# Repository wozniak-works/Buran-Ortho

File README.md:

# Buran-Ortho
A 39-key orthogonal keyboard with support for two knobs.
Forked version with hotswap sockets.

Used License :: [Cern Open hardware](/LICENSE)

---

## Status :: 
- Rev 3 released
- Case options were updated accordingly 
- untested LED-Pinout 

---

## Features :: 
- PCB supports MX, Alps and Choc v1 switches  
- QMK and Vial Support
- built with rp2040 and additional flash storage allowing for plenty of combos, layers, led matrices etc.
- easy to order with jlcpcb --> check release for files 
- support up to two encoders 
- additional pinouts for further modifications 
- - technically could fit an OLED or some other additional parts
- gasket mounted case
- case designed for 3d printing 
- several layout-options for middle part.

## Layout :: 
Below all possible layouts can be observed. All the observed layouts can be choosen and used with Vial or Qmk 

## Case :: 
All files for the case are to be found [here](/case/). 

For the top-part of the case there are several options available, where each of them was designed for a specific layout. 

Another **beautiful** case is to be found [here](https://github.com/subottimale/Buran-Bofa-case). Maybe consider it, seems to be constructed better overall.

## Firmware :: 

the pre-compiled file for Vial and the whole Qmk-userspace for this keyboard can be found [here](/firmware/)

To enter the bootloader - which is necessary in order to flash a new firmware - press the button next to the encoder on the back of the pcb and plug-it into your keyboard while keeping the button pressed. It should show up as a regular usb-stick in your file explorer now and you can drag the .utf onto this usb-stick. Once done it will restart and use your newly flashed firmware!

--- 

## Building your own :: 

On the verge to build this keyboard your own?
Below you can find a little guideline on what is required and how to obtain everything: 

### Getting PCBs ::
in the directory **production** you can find both the gerber and POS-Files required for assembly. 
I usually use JLCPCB for my prototypes, the procedure should be fairly similiar for other manufacturers however, and they require the gerber_buran_pcb.zip and for assembly of all SMD-components also their positions (buran-pos-bottom.csv) and the BOM (buran-BOM.csv) all of which can be found in the **production/assembly** directory. 

### Building Case :: 
The case consists of three parts: the bottom-part, top-part (various layouts available) and the plate. 
Print all of them yourself or have someone print them for your (JLCPCB also offers MFJ printing which could be used (**althought untested!**)).
Now to assemble the case you further need:
| Part | Quantity |
|------|----------|
|2mm thick foam to use as gasket| 14x cut pieces | 
| 20mm M3 | 8x | 

> The length for the Gasket can be taken from the existing cutouts in the case 

As alternative one could also replace the screws with small 3mm diameter magnets. 

### Building the board ::
1. Prepare your pcb accordingly. 
2. Further add the plate and position your switches with them, later solder them to the pcb. 
3. add any feature, like LEDS or knobs. 
4. add **the cut foam** to each lip of the plate. It ought to be positioned both at the top and bottom of the plate --> to isolate properly from the rest of the case!
5. Position everything and screw the case together. 
6. Run Vial on your system and configure the keyboard accordingly 

## Images of Case :: 

Case-option for additional acrylic : 

Case-option without additoinal buttons in the middle : 

Image by Isp 

Case-option with an alternative bottom design :

Design and Image by DeadCatAlive

## Images of PCB ::

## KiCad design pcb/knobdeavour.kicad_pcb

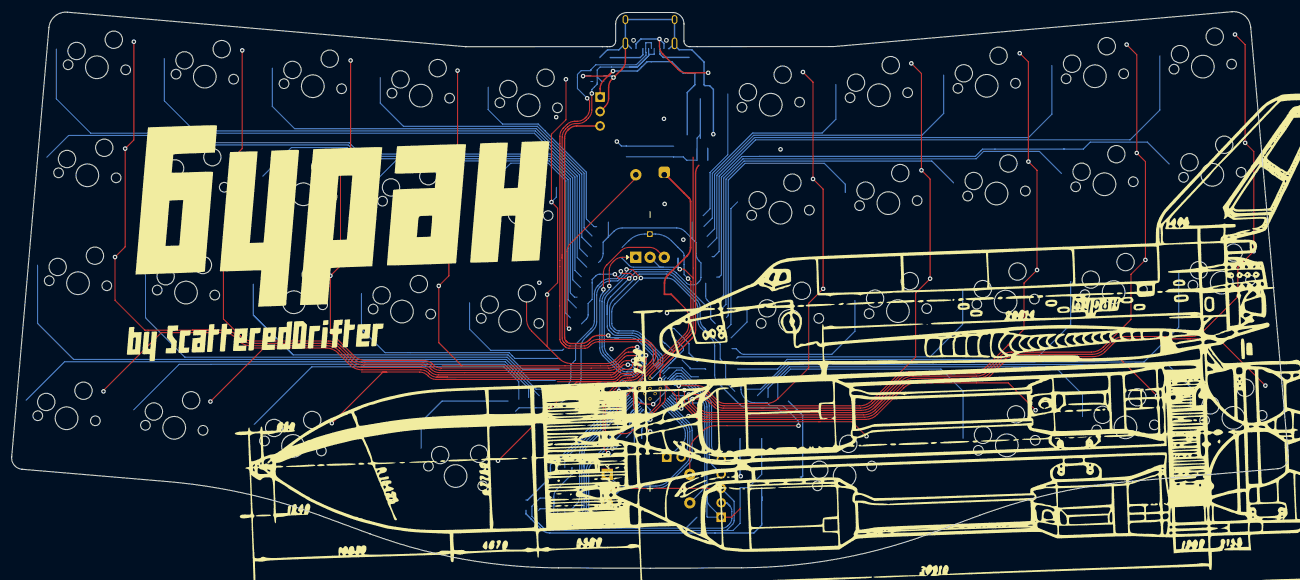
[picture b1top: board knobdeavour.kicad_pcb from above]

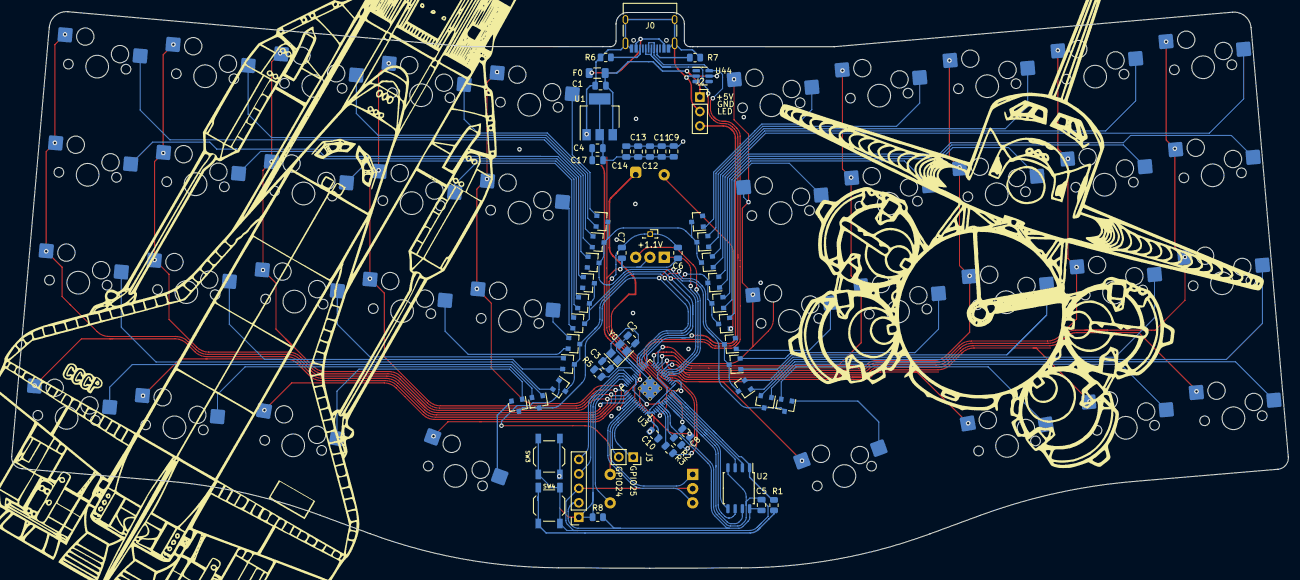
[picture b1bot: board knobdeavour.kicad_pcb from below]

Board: 2 copper layers, 224.4 x 97.8 mm, 97 parts (57 on the bottom side), 87 nets.

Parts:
C1, C4, C17: 10u; C_0805_2012Metric
C2, C3: 22pf; C_0805_2012Metric
C5, C6, C7, C9, C11, C12, C13, C14: 100n; C_0805_2012Metric
C8, C10: 1u; C_0805_2012Metric
D1, D2, D3, D4, D5, D6, D7, D8, D9, D10, D11, D12, D13, D14, D15, D16, D17, D18, D19, D20, D21, D22: BAV70; SOT-23
F0: polyfuse; Fuse_1206_3216Metric
J0: USB_C_Receptacle_USB2.0; USB_C_Receptacle_HRO_TYPE-C-31-M-12
J1: BREAKOUT; PinSocket_1x05_P2.54mm_Vertical
J2: Conn_01x03_Male; PinSocket_1x03_P2.54mm_Vertical
J3: Conn_01x02_Female; PinSocket_1x02_P2.54mm_Vertical
J4: Conn_01x01_Male; PinSocket_1x01_P1.27mm_Vertical
K1, K2, K3, K4, K5, K6, K7, K8, K9, K10, K11, K12, K13, K14, K15, K16, K17, K18, K19, K20, K24, K25, K26, K27, K28, K29, K30, K31, K32, K33, K34, K35, K36, K37, K38, K39, K40, K41: KEYSW; MX100H_modified
R1, R5: 1k; R_0805_2012Metric
R2, R3: 27; R_0805_2012Metric
R6, R7: 5.1k; R_0805_2012Metric
R8: 10K; R_0805_2012Metric
SW1, SW2: RotaryEncoder_Switch; RotaryEncoder_EC11
SW3: SW_PUSH; SW_SPST_TL3342
SW4: RESET; SW_SPST_TL3342
U1: NCP1117-3.3_SOT223; SOT-223-3_TabPin2
U2: W25Q128JVS; SOIC-8_5.23x5.23mm_P1.27mm
U3: RP2040; RP2040-QFN-56
U44: SRV05-4; SOT-23-6
Y0: 12MHZ Crystal; Crystal_SMD_3225-4Pin_3.2x2.5mm

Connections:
+1V1: C6.1, C7.1, C8.1, J4.1, U3.23 (DVDD), U3.45 (VREG_VOUT), U3.50 (DVDD)
+3V3: C4.1, C5.1, C9.1, C10.1, C11.1, C12.1, C13.1, C14.1, C17.1, J1.2, R8.2, U1.2 (VO), U2.8 (VCC), U3.1 (IOVDD), U3.10 (IOVDD), U3.22 (IOVDD), U3.33 (IOVDD), U3.42 (IOVDD), U3.43 (ADC_AVDD), U3.44 (VREG_IN), U3.48 (USB_VDD), U3.49 (IOVDD)
+5V: C1.1, F0.2, J2.1, U1.3 (VI), U44.5 (VP)
/QSPI_SCLK: U2.6 (CLK), U3.52 (QSPI_SCLK)
/QSPI_SD0: U2.5 (DI(IO0)), U3.53 (QSPI_SD0)
/QSPI_SD1: U2.2 (DO(IO1)), U3.55 (QSPI_SD1)
/QSPI_SD2: U2.3 (IO2), U3.54 (QSPI_SD2)
/QSPI_SD3: U2.7 (IO3), U3.51 (QSPI_SD3)
/QSPI_SS: R1.1, U2.1 (~CS), U3.56 (QSPI_SS)
/RUN: J1.1, R8.1, SW3.2, U3.26 (RUN)
/SWCLK: J1.5, U3.24 (SWCLK)
/SWD: J1.4, U3.25 (SWD)
/USB_D+: J0.A6 (D+), J0.B6 (D+), R2.1, U44.3 (IO2)
/USB_D-: J0.A7 (D-), J0.B7 (D-), R3.1, U44.6 (IO4)
/XIN: C2.1, U3.20 (XIN), Y0.3
/XOUT: R5.1, U3.21 (XOUT)
/~USB_BOOT: R1.2, SW4.2
COL0: K1.1, K2.1, K3.1, K4.1, U3.9 (GPIO7)
COL1: K5.1, K6.1, K7.1, K8.1, U3.11 (GPIO8)
COL2: K9.1, K10.1, K11.1, K12.1, U3.12 (GPIO9)
COL3: K13.1, K14.1, K15.1, K16.1, U3.14 (GPIO11)
COL4: K17.1, K18.1, K19.1, U3.13 (GPIO10)
COL5: SW2.S1, U3.2 (GPIO0)
COL6: K25.1, K26.1, K27.1, K28.1, U3.28 (GPIO17)
COL7: K29.1, K30.1, K31.1, K32.1, U3.29 (GPIO18)
COL8: K33.1, K34.1, K35.1, K36.1, U3.30 (GPIO19)
COL9: K37.1, K38.1, K39.1, K40.1, U3.31 (GPIO20)
COL10: K20.1, K24.1, K41.1, U3.32 (GPIO21)
GND: C1.2, C2.2, C3.2, C4.2, C5.2, C6.2, C7.2, C8.2, C9.2, C10.2, C11.2, C12.2, C13.2, C14.2, C17.2, J0.A1 (GND), J0.A12 (GND), J0.B1 (GND), J0.B12 (GND), J0.S1 (SHIELD), J1.3, J2.2, R6.2, R7.2, SW1.C, SW2.C, SW3.1, SW4.1, U1.1 (GND), U2.4 (GND), U3.19 (TESTEN), U3.57 (GND), U44.2 (VN), Y0.2, Y0.4
KNOB2_L: SW2.A, U3.7 (GPIO5)
KNOB2_R: SW2.B, U3.6 (GPIO4)
KNOB2_ROW: D10.1 (A), SW2.S2
KNOB_COL: SW1.S1, U3.27 (GPIO16)
KNOB_DIODE: D22.1 (A), SW1.S2
KNOB_L: SW1.A, U3.35 (GPIO23)
KNOB_R: SW1.B, U3.34 (GPIO22)
LED_GLOW: J2.3, U3.15 (GPIO12)
unnamed: C3.1, R5.2, Y0.1
unnamed: D1.1 (A), K1.2
unnamed: D1.2 (A), K5.2
unnamed: D2.1 (A), K6.2
unnamed: D2.2 (A), K2.2
unnamed: D3.1 (A), K3.2
unnamed: D3.2 (A), K7.2
unnamed: D4.1 (A), K8.2
unnamed: D4.2 (A), K4.2
unnamed: D5.1 (A), K9.2
unnamed: D5.2 (A), K13.2
unnamed: D6.1 (A), K14.2
unnamed: D6.2 (A), K10.2
unnamed: D7.1 (A), K11.2
unnamed: D7.2 (A), K15.2
unnamed: D8.1 (A), K16.2
unnamed: D8.2 (A), K12.2
unnamed: D9.1 (A), K17.2
unnamed: D10.2 (A), K18.2
unnamed: D11.1 (A), K19.2
unnamed: D12.1 (A), K20.2
unnamed: D13.1 (A), K25.2
unnamed: D13.2 (A), K29.2
unnamed: D14.1 (A), K30.2
unnamed: D14.2 (A), K26.2
unnamed: D15.1 (A), K27.2
unnamed: D15.2 (A), K31.2
unnamed: D16.1 (A), K32.2
unnamed: D16.2 (A), K28.2
unnamed: D17.1 (A), K33.2
unnamed: D17.2 (A), K37.2
unnamed: D18.1 (A), K38.2
unnamed: D18.2 (A), K34.2
unnamed: D19.1 (A), K35.2
unnamed: D19.2 (A), K39.2
unnamed: D20.1 (A), K40.2
unnamed: D20.2 (A), K36.2
unnamed: D21.1 (A), K24.2
unnamed: D22.2 (A), K41.2
unnamed: J0.A5 (CC1), R7.1
unnamed: J0.B5 (CC2), R6.1
unnamed: R2.2, U3.47 (USB_DP)
unnamed: R3.2, U3.46 (USB_DM)
ROW0: D1.3 (K), D5.3 (K), D9.3 (K), D12.3 (K), D13.3 (K), D17.3 (K), U3.8 (GPIO6)
ROW1: D2.3 (K), D6.3 (K), D10.3 (K), D14.3 (K), D18.3 (K), D21.3 (K), U3.16 (GPIO13)
ROW2: D3.3 (K), D7.3 (K), D11.3 (K), D15.3 (K), D19.3 (K), D22.3 (K), U3.17 (GPIO14)
ROW3: D4.3 (K), D8.3 (K), D16.3 (K), D20.3 (K), U3.18 (GPIO15)
VBUS: F0.1, J0.A4 (VBUS), J0.A9 (VBUS), J0.B4 (VBUS), J0.B9 (VBUS)
additional_pin1: J3.2, U3.36 (GPIO24)
additional_pin2: J3.1, U3.37 (GPIO25)

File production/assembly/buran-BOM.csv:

Designator,Footprint,Quantity,Value,LCSC Part #
"C1, C17, C4",0805,3,10u,C91245
"C10, C8",0805,2,1u,C28323
"C11, C12, C13, C14, C5, C6, C7, C9",0805,8,100n,C49678
"C2, C3",0805,2,22pf,C1804
"D1, D10, D11, D12, D13, D14, D15, D16, D17, D18, D19, D2, D20, D21, D22, D3, D4, D5, D6, D7, D8, D9",SOT-23,22,BAV70,C68978
F0,1206,1,polyfuse,C69688
J0,USB_C_Receptacle_HRO_TYPE-C-31-M-12,1,USB_C_Receptacle_USB2.0,C165948
J1,PinSocket_1x05_P2.54mm_Vertical,1,BREAKOUT,
J2,PinSocket_1x03_P2.54mm_Vertical,1,Conn_01x03_Male,
J3,PinSocket_1x02_P2.54mm_Vertical,1,Conn_01x02_Female,
J4,PinSocket_1x01_P1.27mm_Vertical,1,Conn_01x01_Male,
"K1, K10, K11, K12, K13, K14, K15, K16, K17, K18, K19, K2, K20, K24, K25, K26, K27, K28, K29, K3, K30, K31, K32, K33, K34, K35, K36, K37, K38, K39, K4, K40, K41, K5, K6, K7, K8, K9",MX100H_modified,38,KEYSW,C41430893
"R1, R5",0805,2,1k,C115316
"R2, R3",0805,2,27,C104170
"R6, R7",0805,2,5.1k,C27834
R8,0805,1,10K,C115309
"SW1, SW2",RotaryEncoder_EC11,2,RotaryEncoder_Switch,
SW3,SW_SPST_TL3342,1,SW_PUSH,C318884
SW4,SW_SPST_TL3342,1,RESET ,C318884
U1,SOT-223-3_TabPin2,1,NCP1117-3.3_SOT223,C26537
U2,SOIC-8_5.23x5.23mm_P1.27mm,1,W25Q128JVS,C97521
U3,RP2040-QFN-56,1,RP2040,C2040
U44,SOT-23-6,1,SRV05-4,C85364
Y0,Crystal_SMD_3225-4Pin_3.2x2.5mm,1,12MHZ Crystal ,C9002

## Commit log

2025-06-14 footprints changed, removed a few tracks
2025-06-14 columns routed
2025-06-14 rows partly routed
2025-06-15 rows routed
2025-06-17 Rouded traces and DRC checked
2025-06-17 Generated production files
2025-06-17 Production files were corrected
2025-06-18 minor ground zone repairs and gerber files generation
